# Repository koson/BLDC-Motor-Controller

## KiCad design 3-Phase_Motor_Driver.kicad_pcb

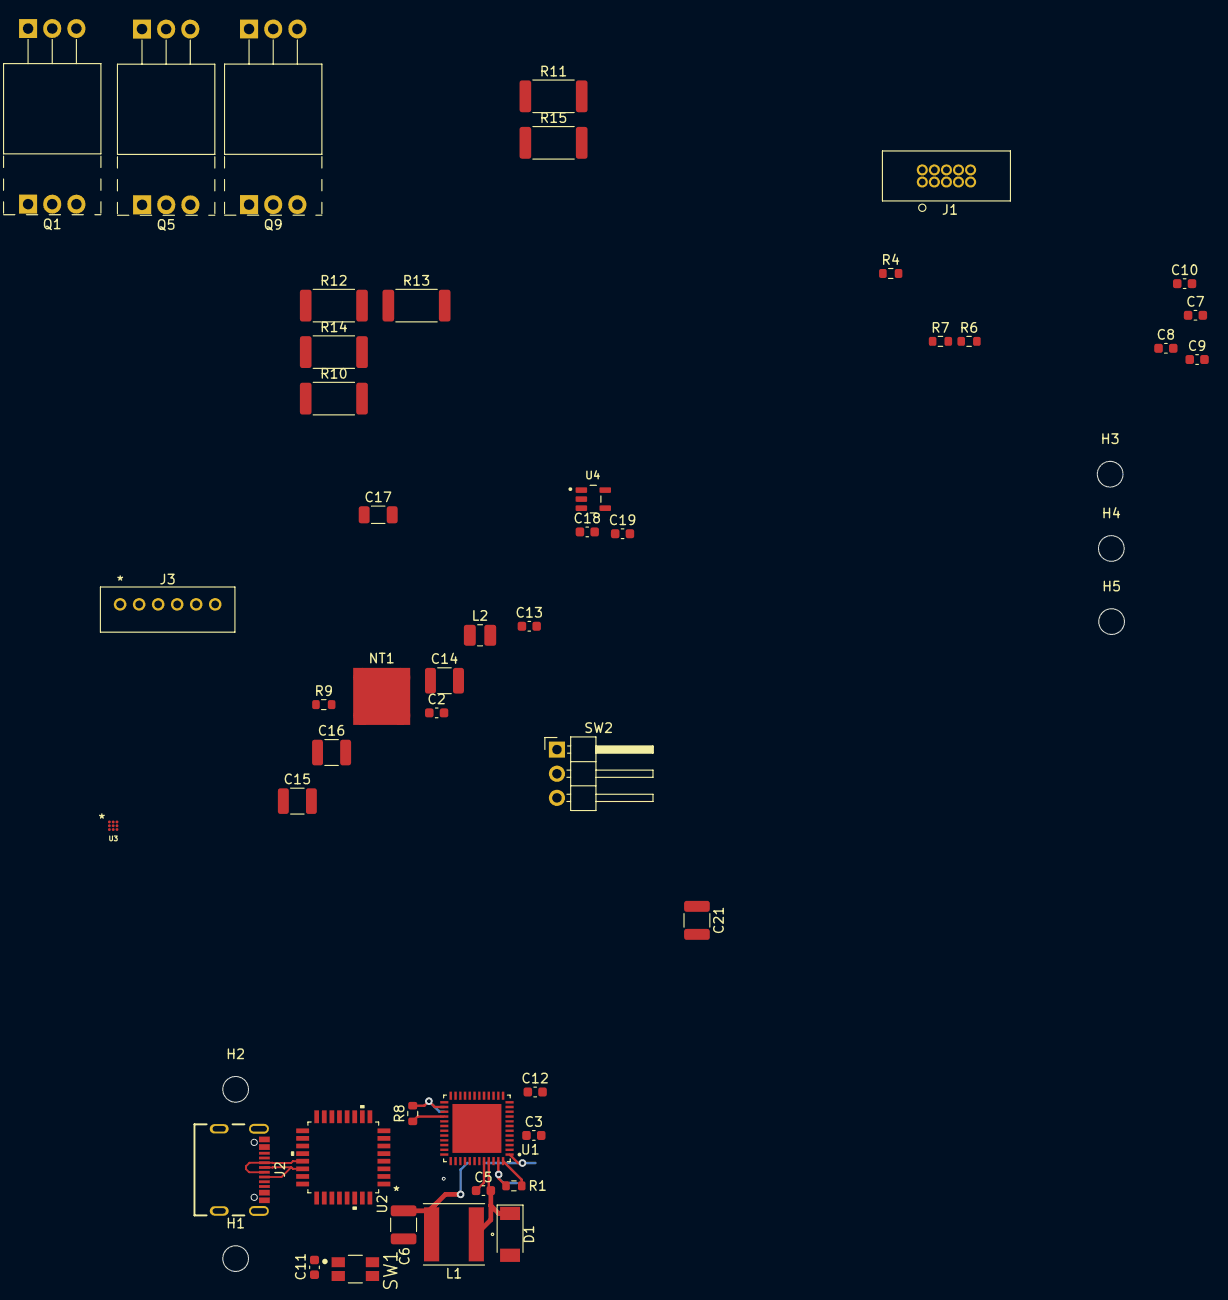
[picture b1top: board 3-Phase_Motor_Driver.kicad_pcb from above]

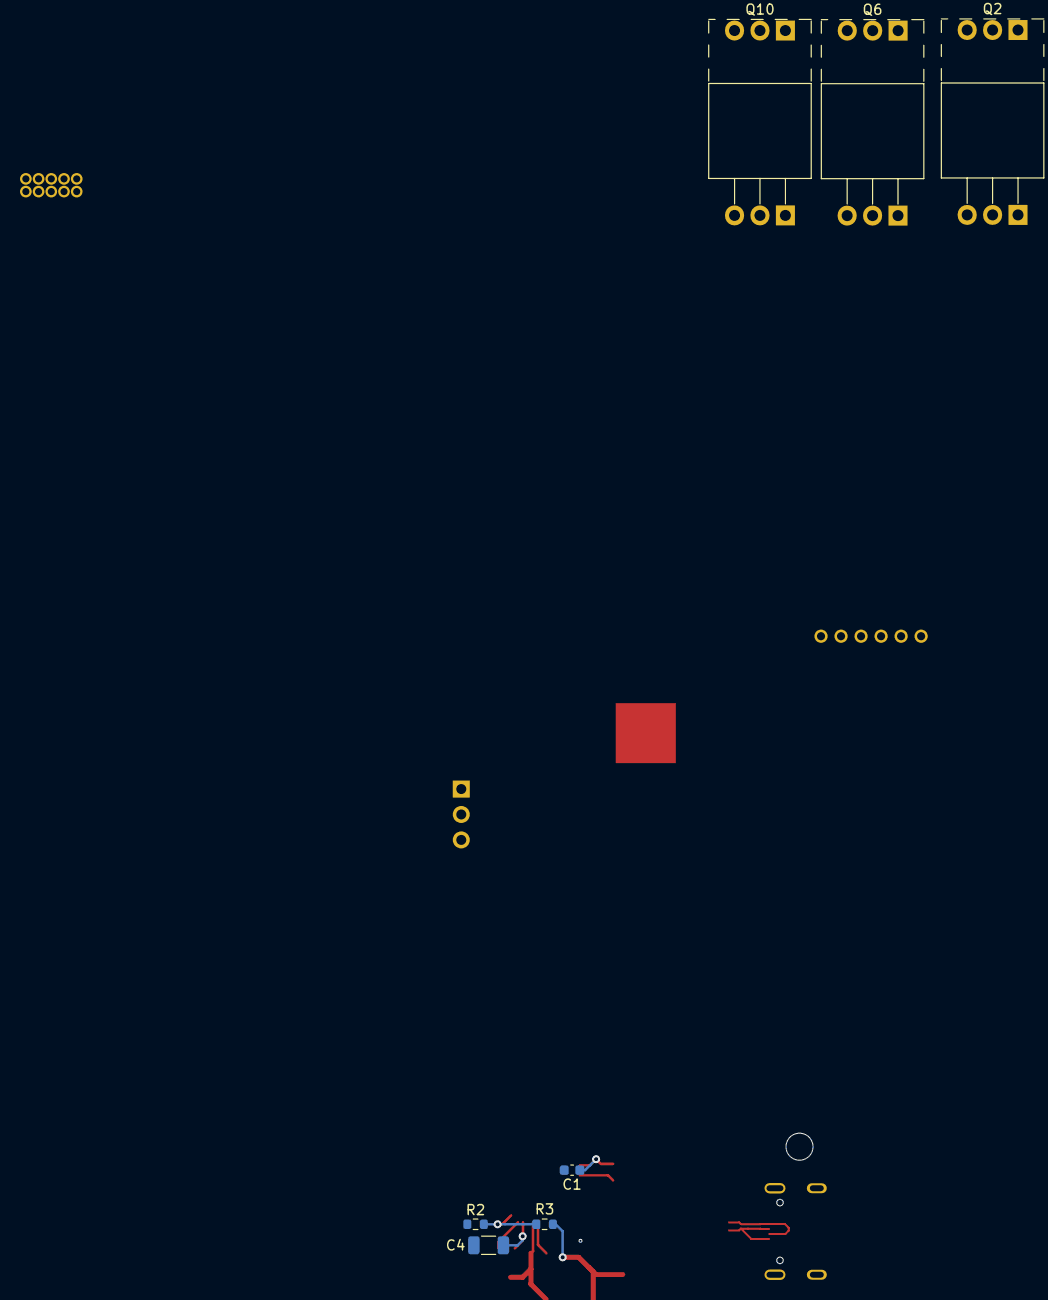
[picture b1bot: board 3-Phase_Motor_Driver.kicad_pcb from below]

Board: 4 copper layers, 58 parts (7 on the bottom side), 56 nets.

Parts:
C1, C2, C3, C5, C10, C18, C19: 1uF/16V; C_0603_1608Metric
C4, C17: 2.2uF/100V/X7R; C_1206_3216Metric
C6, C14, C15, C16, C21: 10uF/X7R/63V; C_1210_3225Metric
C7, C8, C9, C11, C13: 100nF/X7R/100V; C_0603_1608Metric
C12: 47nF/X7R/50V; C_0603_1608Metric
D1: 60V 1A; D_SOD-128
H1, H2, H3, H4, H5: MountingHole_Pad; MountingHole_2.7mm
J1: Conn_02x05_Odd_Even; 3220-10-0100-00
J2: USB4105-GF-A; GCT_USB4105-GF-A
J3: Conn_01x06_Male; B6B-PH-K-SLFSN
L1: 33uH; ASPI-0628-4R7M-T1
L2: 0.47uH/1A; L_1008_2520Metric
NT1: NetTie_2; NetTie-4_SMD_Pad2.0mm
Q1, Q2, Q5, Q6, Q9, Q10: IRF1010EPBF; TO-220-3_Horizontal_TabUp
R1: 100K/1%/0.1W; R_0603_1608Metric
R2: 33.2K/1%/0.1W; R_0603_1608Metric
R3, R4, R6, R7, R8, R9: 10k/1%/0.1W; R_0603_1608Metric
R10, R11, R12, R13, R14, R15: 1L0/2W/1%; R_2512_6332Metric
SW1: EVQ-P7J01P; SW_EVQ-P7J01P
SW2: Boot0; PinHeader_1x03_P2.54mm_Horizontal
U1: DRV8323RSRGZR; QFN50P700X700X100-49N
U2: STM32G441KBT6; STM32G441KBT3
U3: FAN48610UC50X
U4: LP5907MFX-3.3/NOPB; SOT95P280X145-5N

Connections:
+3V3: C19.1, U4.5 (OUT)
+5V: C16.1, J3.6, U3.A1 (VOUT), U3.A2 (VOUT)
CAL: U1.34 (CAL), U2.2 (PF0-OSC_IN)
CS: U1.32 (SCS_N), U2.25 (PA15)
DIR: U1.41 (INHC), U2.30 (PB7)
DVDD: C2.2, U1.36 (DVDD)
ENABLE: U1.33 (ENABLE), U2.12 (PA7)
FAULT: R8.2, U1.28 (FAULT_N)
GHA: Q1.1 (G), U1.8 (GHA)
GHB: Q5.1 (G), U1.17 (GHB)
GHC: Q9.1 (G), U1.18 (GHC)
GLA: Q2.1 (G), U1.10 (GLA)
GLB: Q6.1 (G), U1.15 (GLB)
GLC: Q10.1 (G), U1.20 (GLC)
GNDD: C7.1, C8.1, C9.1, C10.1, C11.2, C16.2, C17.2, C18.2, C19.2, J1.3, J1.5, J1.7, J1.9, J2.A1_B12 (GND), J2.B1_A12 (GND), J2.S1 (SHELL_GND), J2.S2 (SHELL_GND), J2.S3 (SHELL_GND), J2.S4 (SHELL_GND), J3.1, NT1.1, R4.1, R7.1, SW1.2_1, SW1.2_2, U1.27 (DGND), U1.35 (AGND), U2.14 (VSSA), U2.16 (VSS), U2.32 (VSS), U3.C1 (PGND), U3.C2 (PGND), U3.C3 (AGND), U4.2 (GND)
HALL_A: J3.4, U2.9 (PA4)
HALL_B: J3.3, U2.10 (PA5)
HALL_C: J3.2, U2.11 (PA6)
MISO: R9.1, U1.29 (SDO), U2.27 (PB4)
MOSI: U1.30 (SDI), U2.28 (PB5)
NRST: C11.1, J1.10, SW1.1_1, SW1.1_2, U2.4 (PG10-NRST)
unnamed: C3.1, U1.5 (VCP)
unnamed: C5.1, U1.44 (CB)
unnamed: C5.2, D1.1 (K), L1.1, U1.45 (SW)
unnamed: C12.1, U1.4 (CPH)
unnamed: C12.2, U1.3 (CPL)
unnamed: C18.1, J2.A4_B9 (VBUS), J2.B4_A9 (VBUS), U4.1 (IN), U4.3 (EN)
unnamed: L2.2, U3.B1 (SW), U3.B2 (SW)
unnamed: R1.2, U1.48 (SHDN_N)
unnamed: R2.2, R3.1, U1.1 (FB)
unnamed: R6.1, R7.2, SW2.1
unnamed: R6.2, U2.31 (PB8-BOOT0)
PWM: U1.37 (INHA), U2.29 (PB6)
S0: U1.38 (INLA), U2.18 (PA8)
S1: U1.39 (INHB), U2.19 (PA9)
S2: U1.40 (INLB), U2.20 (PA10)
SCK: U1.31 (SCLK), U2.26 (PB3)
SHA: Q1.3 (S), Q2.2 (D), U1.9 (SHA)
SHB: Q5.3 (S), Q6.2 (D), U1.16 (SHB)
SHC: Q9.3 (S), Q10.2 (D), U1.19 (SHC)
SNA: C1.2, C2.1, C4.1, C6.1, C13.2, C14.2, C15.2, C21.2, D1.2 (A), NT1.2, R2.1, R10.2, R11.1, R12.2, R13.1, R14.2, R15.1, U1.2 (PGND), U1.12 (SNA), U1.13 (SNB), U1.22 (SNC), U1.43 (BGND), U1.49 (EP)
SOA: U1.25 (SOA), U2.5 (PA0)
SOB: U1.24 (SOB), U2.6 (PA1)
SOC: U1.23 (SOC), U2.7 (PA2)
SPA: Q2.3 (S), R10.1, R11.2, U1.11 (SPA)
SPB: Q6.3 (S), R12.1, R13.2, U1.14 (SPB)
SPC: Q10.3 (S), R14.1, R15.2, U1.21 (SPC)
SWCLK: J1.4, U2.24 (PA14)
SWDIO: J1.2, U2.23 (PA13)
Switched_Power: C7.2, C8.2, C9.2, C10.2, J1.1, R4.2, SW2.2, U2.1 (VDD), U2.15 (VDDA), U2.17 (VDD)
TEMP: J3.5, U2.8 (PA3)
USB+: J2.A6 (DP1), J2.B6 (DP2), U2.22 (PA12)
USB-: J2.A7 (DN1), J2.B7 (DN2), U2.21 (PA11)
VIN: C3.2, C4.2, C13.1, C14.1, C15.1, C21.1, Q1.2 (D), Q5.2 (D), Q9.2 (D), R1.1, U1.6 (VM), U1.7 (VDRAIN), U1.47 (VIN)
VREF: C1.1, C6.2, C17.1, L1.2, L2.1, R3.2, R8.1, R9.2, U1.26 (VREF), U3.A3 (VIN), U3.B3 (EN)
nBrake: U1.42 (INLC), U2.13 (PB0)

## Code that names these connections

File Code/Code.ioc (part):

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Mcu.Name=STM32G441KBTx
Mcu.Package=LQFP32
Mcu.UserName=STM32G441KBTx
PA0.Mode=IN1-Single-Ended
PA0.Signal=ADC1_IN1
PA1.Mode=IN2-Single-Ended
PA1.Signal=ADC1_IN2
PA11.Mode=Device
PA11.Signal=USB_DM
PA12.Mode=Device
PA12.Signal=USB_DP
PA13.Mode=Serial_Wire
PA13.Signal=SYS_JTMS-SWDIO
PA14.Mode=Serial_Wire
PA14.Signal=SYS_JTCK-SWCLK
PA15.Mode=NSS_Signal_Hard_Output
PA15.Signal=SPI3_NSS
PA2.Mode=IN3-Single-Ended
PA2.Signal=ADC1_IN3
PA3.Mode=IN4-Single-Ended
PA3.Signal=ADC1_IN4
PB3.Mode=Full_Duplex_Master
PB3.Signal=SPI3_SCK
PB4.Mode=Full_Duplex_Master
PB4.Signal=SPI3_MISO
PB5.Mode=Full_Duplex_Master
PB5.Signal=SPI3_MOSI
PB6.Signal=S_TIM8_CH1
RCC.HSE_VALUE=8000000
RCC.SYSCLKFreq_VALUE=160000000
RCC.SYSCLKSource=RCC_SYSCLKSOURCE_PLLCLK
board=custom

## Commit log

2022-05-24 First commit
    Initial commit of files already created
2022-05-31 Added more to schematic
2022-06-20 Updated Schematics and worked on board layout

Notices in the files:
parts and their libraries:
Copyright 2021 Accelerated Designs. All rights reserved.
